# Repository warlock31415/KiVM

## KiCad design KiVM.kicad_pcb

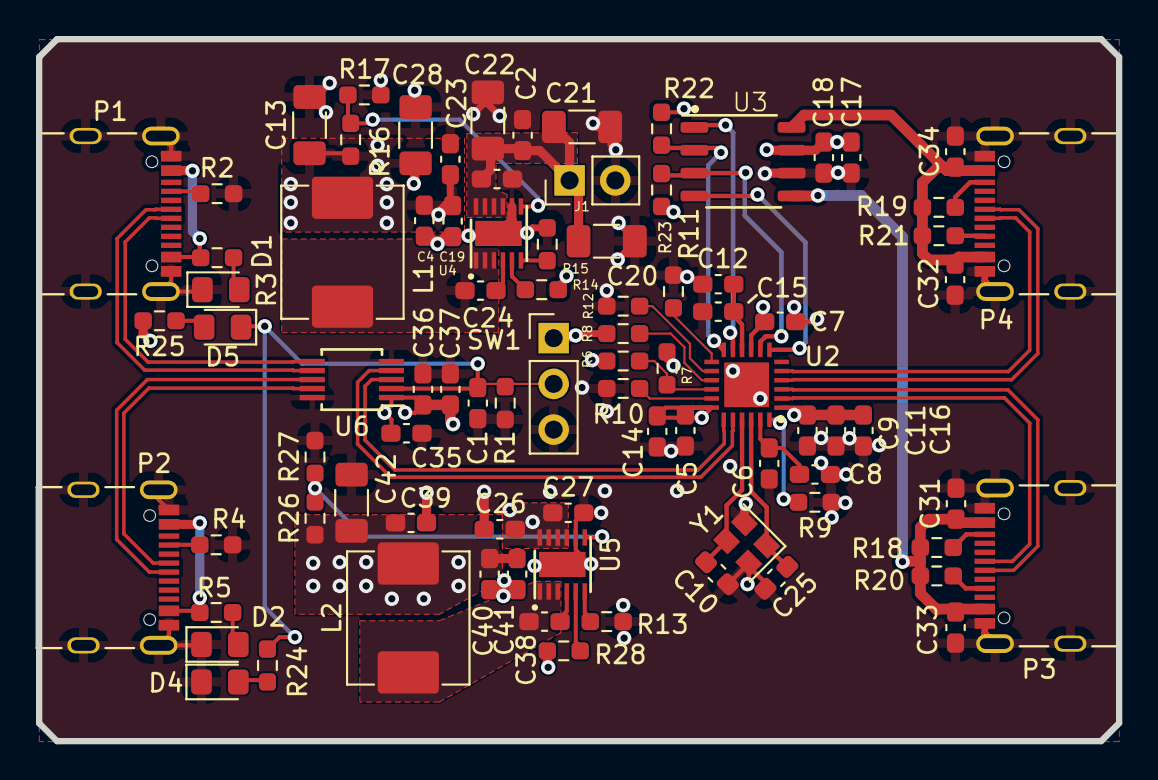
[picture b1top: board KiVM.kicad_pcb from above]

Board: 4 copper layers, 60.0 x 39.0 mm, 86 parts (0 on the bottom side), 53 nets.

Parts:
C1, C3, C4, C8, C11, C14, C15, C17, C18, C19, C24, C26, C27, C33, C34, C36, C37, C38, C40, C41: 0.1uF; C_0603_1608Metric_Pad1.08x0.95mm_HandSolder
C2, C16, C23, C31, C32, C35, C39: 1uF; C_0603_1608Metric_Pad1.08x0.95mm_HandSolder
C5, C6, C7, C9, C12: 1000pF; C_0603_1608Metric_Pad1.08x0.95mm_HandSolder
C10, C25: 18pF; C_0603_1608Metric_Pad1.08x0.95mm_HandSolder
C13, C20, C21, C22, C28, C42: 10uF; C_1206_3216Metric_Pad1.33x1.80mm_HandSolder
D1, D2, D4, D5: GREEN; D_0805_2012Metric_Pad1.15x1.40mm_HandSolder
J1: PJ-037A; PinHeader_1x02_P2.54mm_Vertical
L1, L2: 4.7uH; L_Abracon_ASPI-0630LR
P1, P2, P3, P4: USB_C_Plug_USB2.0; AMPHENOL_12402012E212A
R1, R8, R10, R11, R12: 10k; R_0603_1608Metric_Pad0.98x0.95mm_HandSolder
R2, R4: 5.1k; R_0603_1608Metric_Pad0.98x0.95mm_HandSolder
R3, R5, R24, R25: 120; R_0603_1608Metric_Pad0.98x0.95mm_HandSolder
R6, R7, R22, R23: 100k; R_0603_1608Metric_Pad0.98x0.95mm_HandSolder
R9: 12k; R_0603_1608Metric_Pad0.98x0.95mm_HandSolder
R13, R15: 23K; R_0603_1608Metric_Pad0.98x0.95mm_HandSolder
R14, R16, R26, R28: 100K; R_0603_1608Metric_Pad0.98x0.95mm_HandSolder
R17: 19.1K; R_0603_1608Metric_Pad0.98x0.95mm_HandSolder
R18, R19, R20, R21: 22K; R_0603_1608Metric_Pad0.98x0.95mm_HandSolder
R27: 32K; R_0603_1608Metric_Pad0.98x0.95mm_HandSolder
SW1: SW_SPDT; PinHeader_1x03_P2.54mm_Vertical
U2: USB2422T/MJ; SQFN24_4X4MC_MCH
U3: AP2176SG-13; Diodes-SO8
U4, U5: LMR51450FNDRRR; TI_DFN12_P0.5
U6: RS2227XN; MSOP-10_3x3mm_P0.5mm
Y1: 24MHz; Crystal_SMD_2520-4Pin_2.5x2.0mm

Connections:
+3V3: C5.1, C7.1, C9.1, C11.1, C14.1, C16.1, C39.1, C40.1, C41.1, C42.1, L2.2, R8.1, R25.2, R26.1, R28.1, SW1.1 (A), U2.1 (VDD), U2.9 (VDD), U2.18 (VDD)
+5V: C4.1, C13.1, C17.1, C18.1, C19.1, C23.1, C26.1, C27.1, C28.1, C35.1, C36.1, C37.1, L1.2, R6.1, R14.1, R16.1, R22.1, R23.1, U3.7 (IN), U5.9 (EN), U5.10 (VIN), U5.11 (VIN), U5.12 (VIN), U6.1 (V+)
+12V: C2.1, C3.1, C20.1, C21.1, C22.1, J1.1, U4.9 (EN), U4.10 (VIN), U4.11 (VIN), U4.12 (VIN)
/KVM/DFP_USB_A.D_N: P1.A7 (D-), U6.6 (HSD1_N)
/KVM/DFP_USB_A.D_P: P1.A6 (D+), U6.7 (HSD1_P)
/KVM/DFP_USB_B.D_N: P2.A7 (D-), U6.8 (HSD2_N)
/KVM/DFP_USB_B.D_P: P2.A6 (D+), U6.9 (HSD2_P)
/KVM/Input Connectors A/VBUS: P1.A4 (VBUS), P1.A9 (VBUS), P1.B4 (VBUS), P1.B9 (VBUS), R3.2
/KVM/Input Connectors B/VBUS: P2.A4 (VBUS), P2.A9 (VBUS), P2.B4 (VBUS), P2.B9 (VBUS), R5.2
/KVM/Output Connectors/UFP_USB1.D_N: P3.A7 (D-), U2.2 (USBM_DWN1)
/KVM/Output Connectors/UFP_USB1.D_P: P3.A6 (D+), U2.3 (USBP_DWN1)
/KVM/Output Connectors/UFP_USB2.D_N: P4.A7 (D-), U2.4 (USBM_DWN2)
/KVM/Output Connectors/UFP_USB2.D_P: P4.A6 (D+), U2.5 (USBP_DWN2)
/KVM/Output Connectors/USP_PWR1: C31.1, C33.1, P3.A4 (VBUS), P3.A9 (VBUS), P3.B4 (VBUS), P3.B9 (VBUS), R18.1, R20.1, U3.5 (OUT2)
/KVM/Output Connectors/USP_PWR2: C32.1, C34.1, P4.A4 (VBUS), P4.A9 (VBUS), P4.B4 (VBUS), P4.B9 (VBUS), R19.1, R21.1, U3.8 (OUT1)
/KVM/SOURCE_SEL: C1.1, D5.1 (K), R1.1, R24.2, SW1.2 (B), U6.2 (SELECT)
/KVM/USB Switch/USB_UP.D_N: U2.20 (USBM_UP), U6.4 (D_N)
/KVM/USB Switch/USB_UP.D_P: U2.19 (USBP_UP), U6.3 (D_P)
/KVM/USB/VBUS_DET: R6.2, R7.1, U2.16 (VBUS-DET)
/Power/3V3_SW: C38.2, L2.1, U5.1 (SW), U5.2 (SW), U5.3 (SW)
/Power/5V_SW: C24.2, L1.1, U4.1 (SW), U4.2 (SW), U4.3 (SW)
/Power/FB_3V3: R26.2, R27.1, U5.7 (FB)
/Power/FB_5V: R16.2, R17.1, U4.7 (FB)
GND: C1.2, C2.2, C3.2, C4.2, C5.2, C6.2, C7.2, C8.2, C9.2, C10.2, C11.2, C12.2, C13.2, C14.2, C15.2, C16.2, C17.2, C18.2, C19.2, C20.2, C21.2, C22.2, C23.2, C25.2, C26.2, C27.2, C28.2, C31.2, C32.2, C33.2, C34.2, C35.2, C36.2, C37.2, C39.2, C40.2, C41.2, C42.2, D1.1 (K), D2.1 (K), D4.1 (K), J1.2, P1.A1 (GND), P1.A12 (GND), P1.B1 (GND), P1.B12 (GND), P1.S1 (SHIELD), P2.A1 (GND), P2.A12 (GND), P2.B1 (GND), P2.B12 (GND), P2.S1 (SHIELD), P3.A1 (GND), P3.A12 (GND), P3.B1 (GND), P3.B12 (GND), P3.S1 (SHIELD), P4.A1 (GND), P4.A12 (GND), P4.B1 (GND), P4.B12 (GND), P4.S1 (SHIELD), R1.2, R2.2, R4.2, R7.2, R9.1, R10.2, R11.2, R12.2, R13.2, R15.2, R17.2, R27.2, SW1.3 (C), U2.25 (VSS), U3.6 (GND), U4.8 (AGND), U4.13 (PGND/DAP), U5.8 (AGND), U5.13 (PGND/DAP), U6.5 (GND), U6.10 (OE_B), Y1.2, Y1.4
unnamed: D1.2 (A), R3.1
unnamed: D2.2 (A), R5.1
unnamed: D4.2 (A), R24.1
unnamed: D5.2 (A), R25.1
unnamed: P1.A5 (CC), R2.1
unnamed: P2.A5 (CC), R4.1
unnamed: P3.A5 (CC), R20.2
unnamed: P3.B5 (VCONN), R18.2
unnamed: P4.A5 (CC), R21.2
unnamed: P4.B5 (VCONN), R19.2
unnamed: C12.1, C15.1, U2.10 (CRFILT)
unnamed: R10.1, U2.17 (NO_REM0)
unnamed: C6.1, C8.1, U2.23 (PLLFILT)
unnamed: U2.7 (PRTPWR1), U3.4 (EN2)
unnamed: U2.11 (PRTPWR2), U3.1 (EN1)
unnamed: R9.2, U2.24 (RBIAS)
unnamed: R12.1, U2.14 (SMBCLK/CFG_SEL0)
unnamed: R11.1, U2.13 (SMBDAT/NO_REM1)
unnamed: C25.1, U2.22 (XTALIN), Y1.1
unnamed: C10.1, U2.21 (XTALOUT), Y1.3
unnamed: R23.2, U2.8 (~OCS1), U3.3 (FLG2_B)
unnamed: R22.2, U2.12 (~OCS2), U3.2 (FLG1_B)
unnamed: R8.2, U2.15 (~RST)
unnamed: C24.1, U4.4 (BOOT)
unnamed: R14.2, U4.5 (PG)
unnamed: R15.1, U4.6 (RT)
unnamed: C38.1, U5.4 (BOOT)
unnamed: R28.2, U5.5 (PG)
unnamed: R13.1, U5.6 (RT)

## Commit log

2022-12-20 Adding flow diagram and USB hub symbol (incomplete)
2022-12-20 Only connectors left
2022-12-20 Adding 5v and 3v3 buck
2022-12-21 fixing sheet numbers and adding schematic PDF
2022-12-23 Fixing ERC
2024-02-01 Pushing what i have now
